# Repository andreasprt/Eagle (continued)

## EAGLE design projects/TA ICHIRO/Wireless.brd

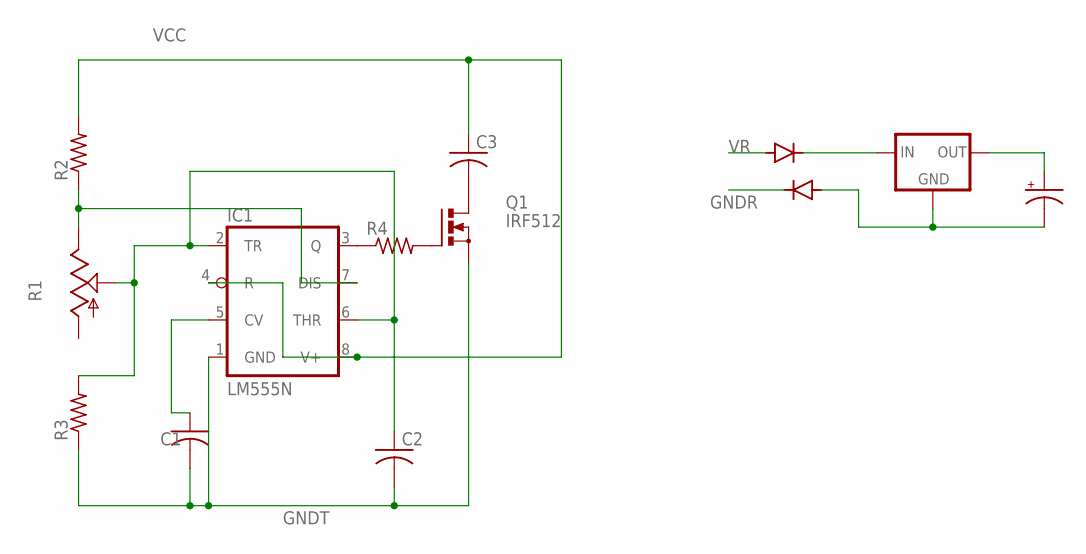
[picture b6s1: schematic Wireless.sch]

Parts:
C1, C2, C3: C-US050-025X075; C050-025X075
C4: CPOL-USE2.5-6; E2,5-6
D1, D2: 1N4004; DO41-10
IC1: LM555N; DIL08-ROUND
IC2: 78XXS
Q1: IRF512; TO220BV
R1: TRIM_US-CA6V; CA6V
R2, R3, R4: R-US_0207/10; 0207/10

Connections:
+: C4.+, IC2.OUT
-: C4.-, D2.A, IC2.GND
GNDR: D2.C
GNDT: C1.2, C2.2, IC1.1 (GND), Q1.S, R3.1
unnamed: IC1.7 (DIS), R1.E, R2.1
unnamed: IC1.3 (Q), R4.1
unnamed: Q1.G, R4.2
unnamed: C2.1, IC1.2 (TR), IC1.6 (THR), R1.S, R3.2
unnamed: C1.1, IC1.5 (CV)
unnamed: D1.C, IC2.IN
OUT: C3.2, Q1.D
VCC: C3.1, IC1.4 (R), IC1.8 (V+), R2.2
VR: D1.A

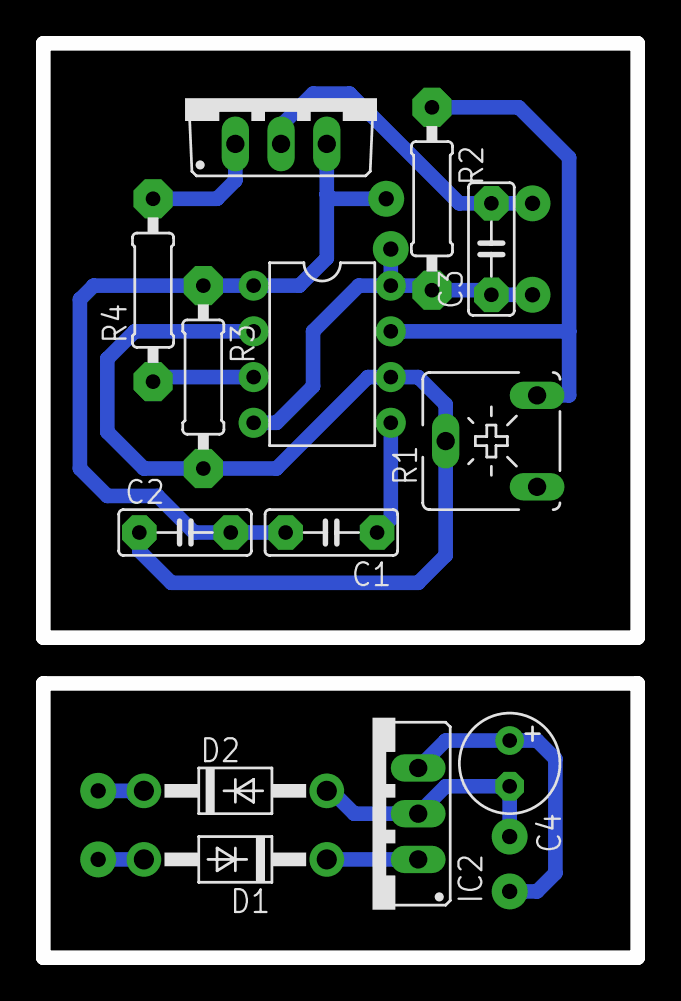
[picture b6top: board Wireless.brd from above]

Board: 2 copper layers, 33.0 x 50.8 mm, 13 parts (0 on the bottom side), 11 nets.
